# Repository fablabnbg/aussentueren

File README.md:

# aussentueren
Hard- and Software for external doors of Hackerspaces

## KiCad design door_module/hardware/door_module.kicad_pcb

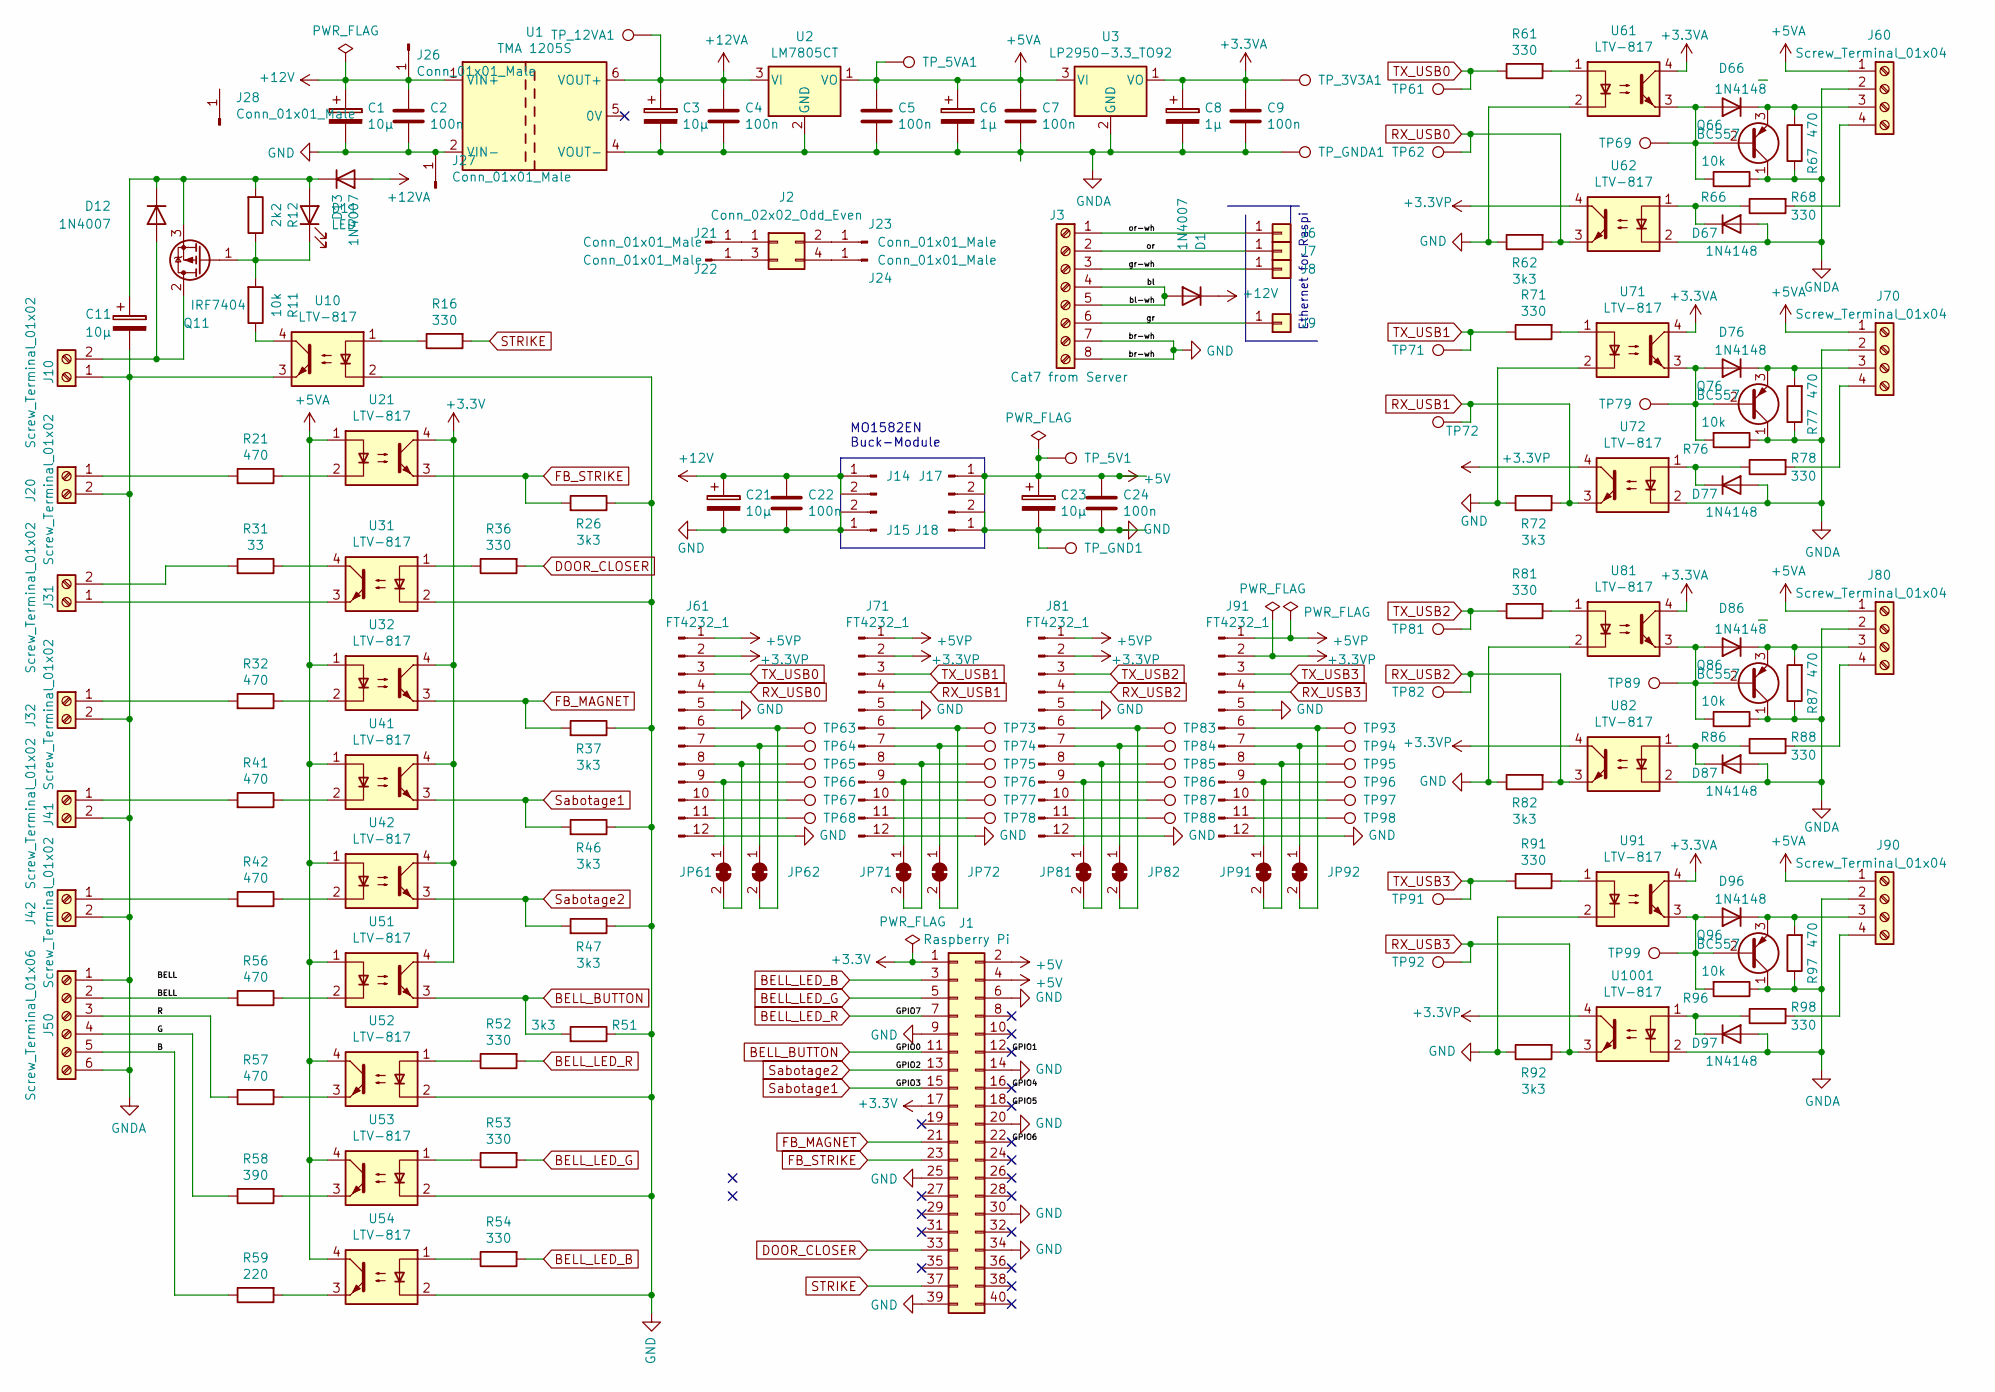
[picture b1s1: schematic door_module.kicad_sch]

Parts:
C1: 10µ; CP_Radial_D13.0mm_P7.50mm
C2, C4, C5, C7, C9: 100n; C_Disc_D3.0mm_W2.0mm_P2.50mm
C3, C11, C21, C23: 10µ; CP_Radial_D14.0mm_P7.50mm
C6: 1µ; CP_Radial_D5.0mm_P2.00mm
C8: 1µ; CP_Radial_Tantal_D5.5mm_P2.50mm
C22, C24: 100n; CP_Radial_D14.0mm_P7.50mm
D1, D12, D13: 1N4007; D_DO-41_SOD81_P10.16mm_Horizontal
D11: LED; LED_D5.0mm
D66, D67, D76, D77, D86, D87, D96, D97: 1N4148; D_DO-35_SOD27_P7.62mm_Horizontal
J1: Raspberry Pi; PinSocket_2x20_P2.54mm_Vertical
J2: Conn_02x02_Odd_Even; PinHeader_2x02_P2.54mm_Vertical
J3: Cat7 from Server; RJ45_Wuerth_7499010121A_Horizontal
J6, J7, J8, J9, J14, J15, J17, J18: SolderWirePad_1x02_P3.81mm_Drill0.8mm
J10, J20, J31, J32, J41, J42: Screw_Terminal_01x02; PhoenixContact_MSTBA_2,5_2-G-5,08_1x02_P5.08mm_Horizontal
J21, J22, J23, J24, J26, J27, J28: Conn_01x01_Male; PinHeader_1x01_P2.54mm_Vertical
J50: Screw_Terminal_01x06; PhoenixContact_MSTBA_2,5_6-G-5,08_1x06_P5.08mm_Horizontal
J60, J70, J80, J90: Screw_Terminal_01x04; PhoenixContact_MSTBA_2,5_4-G-5,08_1x04_P5.08mm_Horizontal
J61, J71, J81, J91: FT4232_1; PinSocket_1x12_P2.54mm_Vertical
JP61, JP62, JP71, JP72, JP81, JP82, JP91, JP92: SolderJumper_2_Bridged; SolderJumper-2_P1.3mm_Bridged_Pad1.0x1.5mm
Q11: IRF7404; TO-220-3_Vertical
Q66, Q76, Q86, Q96: BC557; TO-92_Inline
R11, R66, R76, R86, R96: 10k; R_Axial_DIN0207_L6.3mm_D2.5mm_P10.16mm_Horizontal
R12: 2k2; R_Axial_DIN0207_L6.3mm_D2.5mm_P10.16mm_Horizontal
R16, R36, R52, R53, R54, R61, R68, R71, R78, R81, R88, R91, R98: 330; R_Axial_DIN0207_L6.3mm_D2.5mm_P10.16mm_Horizontal
R21, R32, R41, R42, R56, R57, R67, R77, R87, R97: 470; R_Axial_DIN0207_L6.3mm_D2.5mm_P10.16mm_Horizontal
R26, R37, R46, R47, R51, R62, R72, R82, R92: 3k3; R_Axial_DIN0207_L6.3mm_D2.5mm_P10.16mm_Horizontal
R31: 33; R_Axial_DIN0207_L6.3mm_D2.5mm_P10.16mm_Horizontal
R58: 390; R_Axial_DIN0207_L6.3mm_D2.5mm_P10.16mm_Horizontal
R59: 220; R_Axial_DIN0207_L6.3mm_D2.5mm_P10.16mm_Horizontal
TP61, TP62, TP63, TP64, TP65, TP66, TP67, TP68, TP69, TP71, TP72, TP73, TP74, TP75, TP76, TP77, TP78, TP79, TP81, TP82, TP83, TP84, TP85, TP86, TP87, TP88, TP89, TP91, TP92, TP93, TP94, TP95, TP96, TP97, TP98, TP99: TestPoint; TestPoint_Loop_D1.80mm_Drill1.0mm_Beaded
TP_3V3A1, TP_5V1, TP_5VA1, TP_12VA1: TestPoint; TestPoint_Loop_D2.60mm_Drill1.6mm_Beaded
TP_GND1: TestPoint; TestPoint_Loop_D2.60mm_Drill1.6mm_Beaded
TP_GNDA1: TestPoint; TestPoint_Loop_D2.60mm_Drill1.6mm_Beaded
U1: TMA 1205S; SIP9_Housing_BigPads
U2: LM7805CT; TO-220-3_Vertical
U3: LP2950-3.3_TO92; TO-92_Inline
U10, U21, U31, U32, U41, U42, U51, U52, U53, U54, U61, U62, U71, U72, U81, U82, U91, U1001: LTV-817; DIP-4_W7.62mm

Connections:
+3.3VA: C8.1, C9.1, TP_3V3A1.1, U3.1 (VO), U61.4, U71.4, U81.4, U91.4
+3.3VP: J61.2, J71.2, J81.2, J91.2, U62.4, U72.4, U82.4, U1001.4
+3V3: J1.1, J1.17, U21.4, U32.4, U41.4, U42.4, U51.4
+5V: C23.1, C24.1, J1.2, J1.4, J17.1, J17.2, TP_5V1.1
+5VA: C5.1, C6.1, C7.1, J60.1, J70.1, J80.1, J90.1, TP_5VA1.1, U2.1 (VO), U3.3 (VI), U21.1, U32.1, U41.1, U42.1, U51.1, U52.4, U53.4, U54.4
+5VP: J61.1, J71.1, J81.1, J91.1
+12V: C1.1, C2.1, C21.1, C22.1, D1.1 (K), J14.1, J14.2, J26.1, U1.1 (VIN+)
+12VA: C3.1, C4.1, D13.2 (A), TP_12VA1.1, U1.6 (VOUT+), U2.3 (VI)
/B: J50.5, R59.1
/BELL: J50.2, R56.2
/G: J50.4, R58.1
/GPIO1: J1.12
/GPIO4: J1.16
/GPIO5: J1.18
/GPIO6: J1.22
/R: J50.3, R57.1
/bl: D1.2 (A), J3.4, J3.5
/gr: J3.6, J9.1
/gr-wh: J3.3, J8.1
/or: J3.2, J7.1
/or-wh: J3.1, J6.1
BELL_BUTTON: J1.11, R51.2, U51.3
BELL_LED_B: J1.3, R54.2
BELL_LED_G: J1.5, R53.2
BELL_LED_R: J1.7, R52.2
DOOR_CLOSER: J1.33, R36.2
FB_MAGNET: J1.21, R37.2, U32.3
FB_STRIKE: J1.23, R26.2, U21.3
GND: C1.2, C2.2, C21.2, C22.2, C23.2, C24.2, J1.6, J1.9, J1.14, J1.20, J1.25, J1.30, J1.34, J1.39, J3.7, J3.8, J15.1, J15.2, J18.1, J18.2, J27.1, J61.5, J61.12, J71.5, J71.12, J81.5, J81.12, J91.5, J91.12, R26.1, R37.1, R46.1, R47.1, R51.1, R62.1, R72.1, R82.1, R92.1, TP_GND1.1, U1.2 (VIN-), U10.2, U31.2, U52.2, U53.2, U54.2, U61.2, U71.2, U81.2, U91.2
GNDA: C3.2, C4.2, C5.2, C6.2, C7.2, C8.2, C9.2, C11.2, D67.2 (A), D77.2 (A), D87.2 (A), D97.2 (A), J10.1, J20.2, J32.2, J41.2, J42.2, J50.1, J50.6, J60.2, J70.2, J80.2, J90.2, Q66.1 (C), Q76.1 (C), Q86.1 (C), Q96.1 (C), R66.2, R67.1, R76.1, R77.1, R86.2, R87.1, R96.1, R97.1, TP_GNDA1.1, U1.4 (VOUT-), U2.2 (GND), U3.2 (GND), U10.3, U62.2, U72.2, U82.2, U1001.2
unnamed: C11.1, D11.2 (A), D12.1 (K), D13.1 (K), Q11.3 (S), R12.2
unnamed: D11.1 (K), Q11.1 (G), R11.2, R12.1
unnamed: D12.2 (A), J10.2, Q11.2 (D)
unnamed: D66.1 (K), J60.3, Q66.3 (E), R67.2
unnamed: D66.2 (A), Q66.2 (B), R66.1, TP69.1, U61.3
unnamed: D67.1 (K), R68.1, U62.1
unnamed: D76.1 (K), J70.3, Q76.3 (E), R77.2
unnamed: D76.2 (A), Q76.2 (B), R76.2, TP79.1, U71.3
unnamed: D77.1 (K), R78.1, U72.1
unnamed: D86.1 (K), J80.3, Q86.3 (E), R87.2
unnamed: D86.2 (A), Q86.2 (B), R86.1, TP89.1, U81.3
unnamed: D87.1 (K), R88.1, U82.1
unnamed: D96.1 (K), J90.3, Q96.3 (E), R97.2
unnamed: D96.2 (A), Q96.2 (B), R96.2, TP99.1, U91.3
unnamed: D97.1 (K), R98.1, U1001.1
unnamed: J2.1, J21.1
unnamed: J2.2, J23.1
unnamed: J2.3, J22.1
unnamed: J2.4, J24.1
unnamed: J20.1, R21.2
unnamed: J31.1, U31.3
unnamed: J31.2, R31.2
unnamed: J32.1, R32.2
unnamed: J41.1, R41.2
unnamed: J42.1, R42.2
unnamed: J60.4, R68.2
unnamed: J61.6, JP62.2 (B), TP63.1
unnamed: J61.7, JP62.1 (A), TP64.1
unnamed: J61.8, JP61.2 (B), TP65.1
unnamed: J61.9, JP61.1 (A), TP66.1
unnamed: J61.10, TP67.1
unnamed: J61.11, TP68.1
unnamed: J70.4, R78.2
unnamed: J71.6, JP72.2 (B), TP73.1
unnamed: J71.7, JP72.1 (A), TP74.1
unnamed: J71.8, JP71.2 (B), TP75.1
unnamed: J71.9, JP71.1 (A), TP76.1
unnamed: J71.10, TP77.1
unnamed: J71.11, TP78.1
unnamed: J80.4, R88.2
unnamed: J81.6, JP82.2 (B), TP83.1
unnamed: J81.7, JP82.1 (A), TP84.1
unnamed: J81.8, JP81.2 (B), TP85.1
unnamed: J81.9, JP81.1 (A), TP86.1
unnamed: J81.10, TP87.1
unnamed: J81.11, TP88.1
unnamed: J90.4, R98.2
unnamed: J91.6, JP92.2 (B), TP93.1
unnamed: J91.7, JP92.1 (A), TP94.1
unnamed: J91.8, JP91.2 (B), TP95.1
unnamed: J91.9, JP91.1 (A), TP96.1
unnamed: J91.10, TP97.1
unnamed: J91.11, TP98.1
unnamed: R11.1, U10.4
unnamed: R16.1, U10.1
unnamed: R21.1, U21.2
unnamed: R31.1, U31.4
unnamed: R32.1, U32.2
unnamed: R36.1, U31.1
unnamed: R41.1, U41.2
unnamed: R42.1, U42.2
unnamed: R52.1, U52.1
unnamed: R53.1, U53.1
unnamed: R54.1, U54.1
unnamed: R56.1, U51.2
unnamed: R57.2, U52.3
unnamed: R58.2, U53.3
unnamed: R59.2, U54.3
unnamed: R61.2, U61.1
unnamed: R71.2, U71.1
unnamed: R81.2, U81.1
unnamed: R91.2, U91.1
RX_USB0: J61.4, R62.2, TP62.1, U62.3
RX_USB1: J71.4, R72.2, TP72.1, U72.3
RX_USB2: J81.4, R82.2, TP82.1, U82.3
RX_USB3: J91.4, R92.2, TP92.1, U1001.3
STRIKE: J1.37, R16.2
Sabotage1: J1.15, R46.2, U41.3
Sabotage2: J1.13, R47.2, U42.3
TX_USB0: J61.3, R61.1, TP61.1
TX_USB1: J71.3, R71.1, TP71.1
TX_USB2: J81.3, R81.1, TP81.1
TX_USB3: J91.3, R91.1, TP91.1

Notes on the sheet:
MO1582EN Buck-Module
Ethernet for Raspi

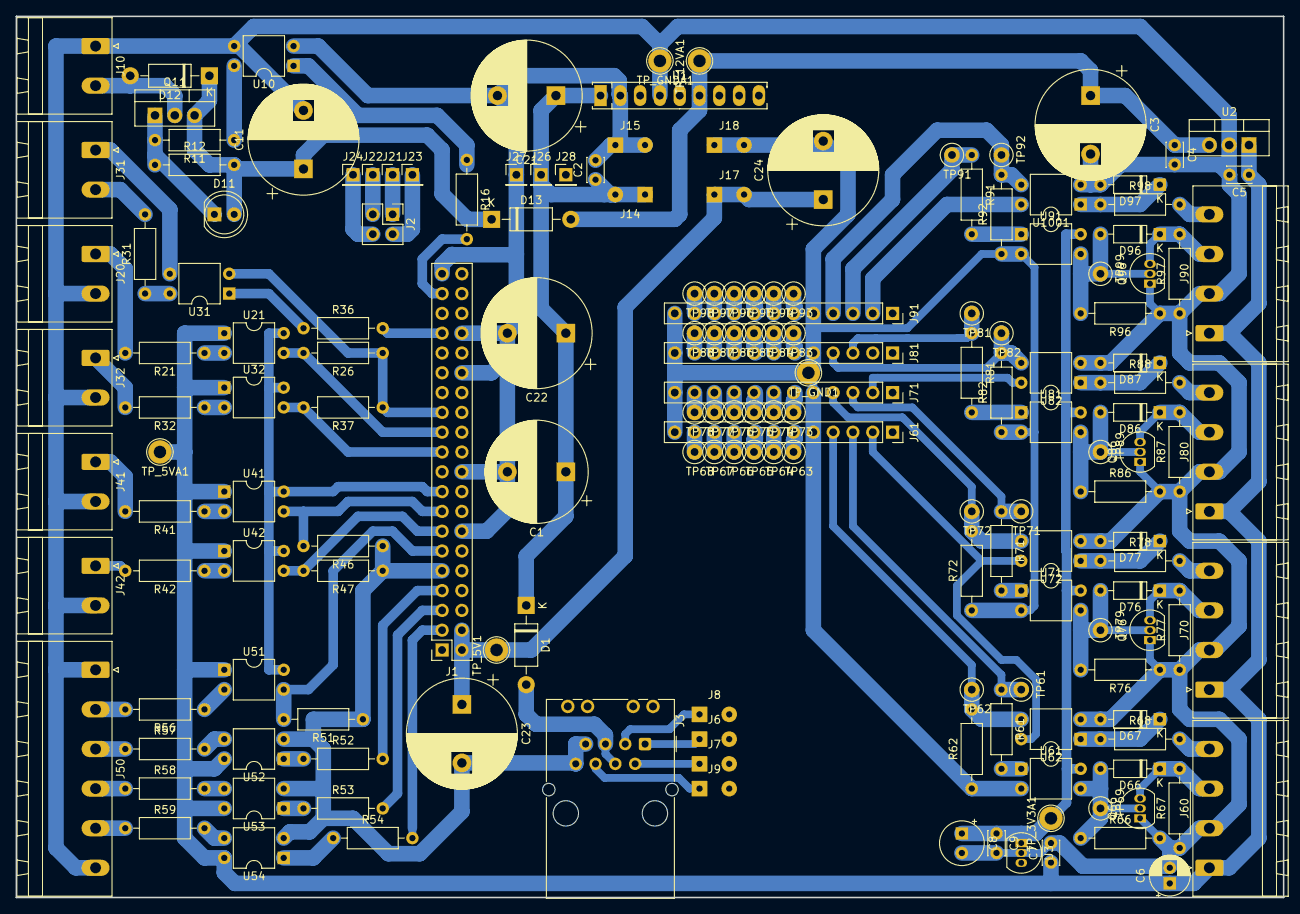
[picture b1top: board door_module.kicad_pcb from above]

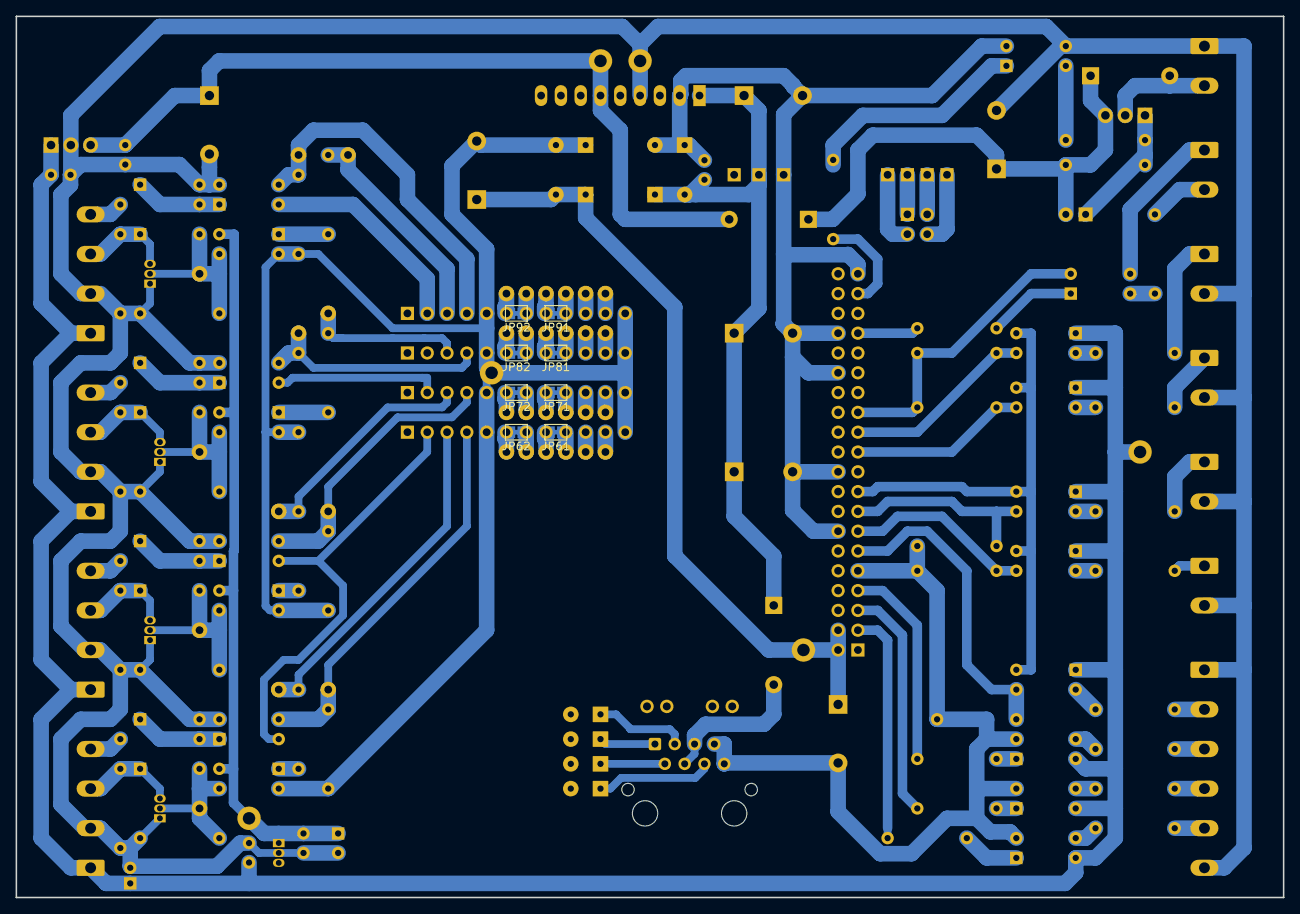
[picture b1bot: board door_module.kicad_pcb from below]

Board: 2 copper layers, 162.6 x 113.0 mm, 176 parts (8 on the bottom side), 109 nets.

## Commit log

2019-02-02 First commit. Door module basically working
2019-02-02 Remove unused imports from main
2019-02-02 Add missing imported file
2019-02-02 remove some logging, add delay after configuration of gpios
2019-02-02 Fix midding argument in on_message callback of mqtt
2019-02-02 Fix message validation
2019-02-03 Get Module-Server communication working
2019-02-03 Add SAK to identity_store
2019-02-03 allow retained mode mqtt messages
2019-02-03 Have beepstyles
2019-02-03 Send card shown message after pin entry
2019-02-03 Warn at unknown beepstyles
2019-02-03 Remove MQTT logging
2019-02-03 Fix beeping in terpreter
2019-02-03 Basic functionality
2019-02-03 Example config
2019-02-03 Example config door_module
2019-02-03 First WIP version
2019-02-03 Remove mqtt-logging in server
2019-02-03 Place message validation in its own class
2019-02-03 Move validator into its own file
2019-02-03 Move validator into common folder
2019-02-03 Fix variable name of validator in server mqtt
2019-02-03 Use same validator in door_module
2019-02-03 Add "common"-folder to door_module
2019-02-03 Fix hmac calculation after validator move
2019-02-03 Fix validator
2019-02-03 Move server message preparation into its own function
2019-02-03 Move message preparation for module into its own function
2019-02-09 Add tests for validator
2019-02-09 Allow validator tests to be run from main software dir
2019-02-09 Add tests for pin handling
2019-02-09 Cleanup imports in pin.py
2019-02-09 Protext keypad buffer with mutex
2019-02-09 Open Keypad serial line in main to improve testability
2019-02-09 Add __init__.py to test dir
2019-02-09 Move config to environment/.env
2019-03-09 Small initial changes to Schematic
2019-03-09 Finalized Alpha Version of Door-Module Schematic
2019-03-10 Change: buffered serial outputs Change: PoE added 25k Resistor Add: Test points Add: Annotations and Values Change: Tidy up things a little
2019-03-11 First Placement of door_module PCB Minor changes to schematic
2019-03-11 Some more Groups on the door_module PCB
2019-04-10 First alpha PCB
2019-11-04 Fix validator. Need to use payload property of mqtt message
2019-11-04 Make main.py of door_server executeable. Monkeypatch fromisodate.
    Python versions below 3.7 do not have fromisodate in datetime.
    This method is added with a backport module
2019-11-04 Add systemd service-files. Fix #5
2019-11-05 Ratelimit NFC reader
2019-11-05 Use logging module instead of prints
2019-11-05 place some values in parameter file
2019-11-05 Log MQTT connection
2019-11-05 Add control of automatic door closer
2019-11-05 Send 'close' command to all doors if close is activated
2019-11-05 Implement 'public'-mode
2019-11-05 Implement 'public'-mode that keeps door unlocked
2019-11-05 Ignore cards on outside if public mode
2019-11-06 Add Sneaky mode and more published MQTT
2019-11-06 Allow for sneaky mode
2019-11-17 locking while public bugfix
2019-11-17 Fixing PIN change to actually work
2023-11-19 automatically downgrade 10er to 5er if expired; allow expiry_date = NULL for 5er
2023-11-30 -mod: Changed U2 VoltegeRegulatior to LM7805CT
2023-12-05 fix and add meaningful log warning messages
